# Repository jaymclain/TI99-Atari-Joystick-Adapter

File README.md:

# Atari Joystick Adapter for the TI-99/4A

Based on the design from Gary Cook - Compute! magazine, August 1983 issue, and other internet resources.

v0.01

**NOTE: THIS PROJECT IS CURRENTLY UNTESTED!**

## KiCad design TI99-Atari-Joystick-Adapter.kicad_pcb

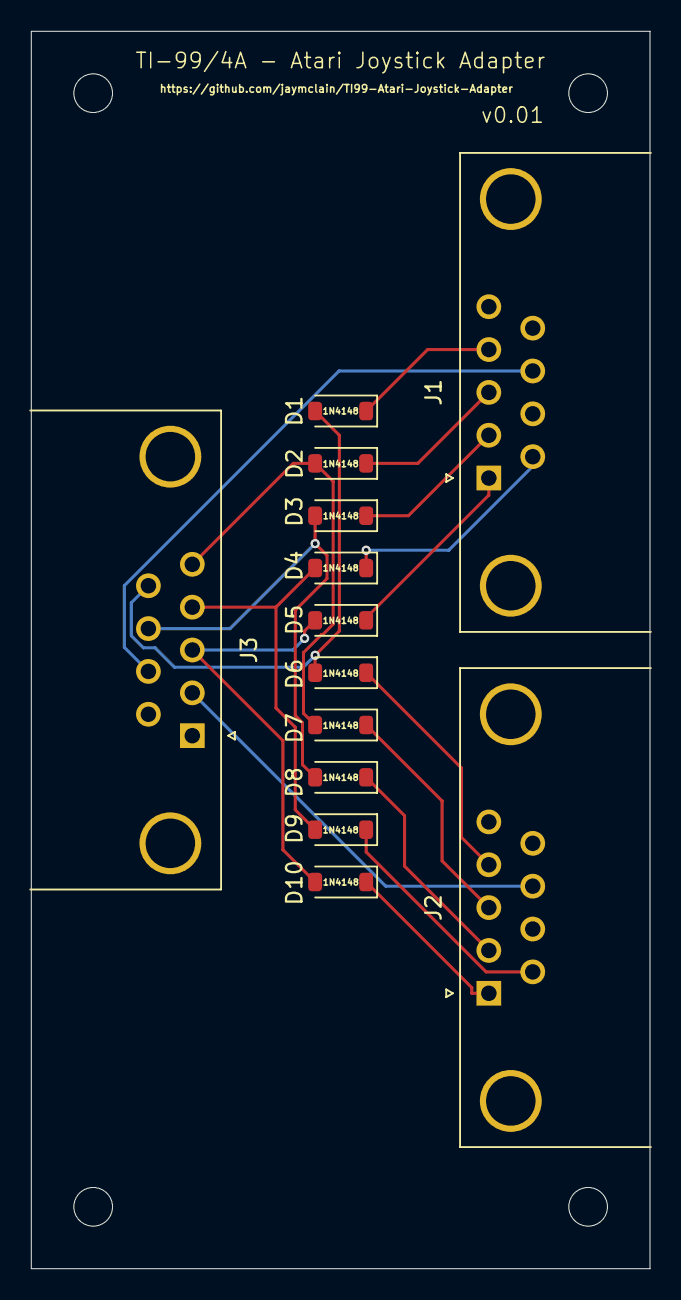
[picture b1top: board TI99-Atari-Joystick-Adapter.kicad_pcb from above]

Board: 2 copper layers, 40.0 x 80.0 mm, 17 parts (0 on the bottom side), 17 nets.

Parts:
D1, D2, D3, D4, D5, D6, D7, D8, D9, D10: 1N4148; D_SOD-123
H1, H2, H3, H4: MountingHole; MountingHole_2.5mm
J1, J2: DE9_Plug_MountingHoles; DSUB-9_Male_Horizontal_P2.77x2.84mm_EdgePinOffset7.70mm_Hou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
J3: DE9_Receptacle_MountingHoles; DSUB-9_Female_Horizontal_P2.77x2.84mm_EdgePinOffset7.70mm_H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

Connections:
unnamed: D1.2 (A), D6.2 (A), J3.9
unnamed: D1.1 (K), J1.4
unnamed: D2.2 (A), D7.2 (A), J3.5
unnamed: D2.1 (K), J1.3
unnamed: D3.2 (A), D8.2 (A), J3.8
unnamed: D3.1 (K), J1.2
unnamed: D4.2 (A), D9.2 (A), J3.4
unnamed: D4.1 (K), J1.6
unnamed: D5.1 (K), J1.1
unnamed: D6.1 (K), J2.4
unnamed: D7.1 (K), J2.3
unnamed: D8.1 (K), J2.2
unnamed: D9.1 (K), J2.6
unnamed: D5.2 (A), D10.2 (A), J3.3
unnamed: D10.1 (K), J2.1
unnamed: J1.8, J3.7
unnamed: J2.8, J3.2

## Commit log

2025-01-28 Initial Design v0.01
2025-01-29 Update board size, add tracks & vias and board image.
2025-03-02 Add render to README
